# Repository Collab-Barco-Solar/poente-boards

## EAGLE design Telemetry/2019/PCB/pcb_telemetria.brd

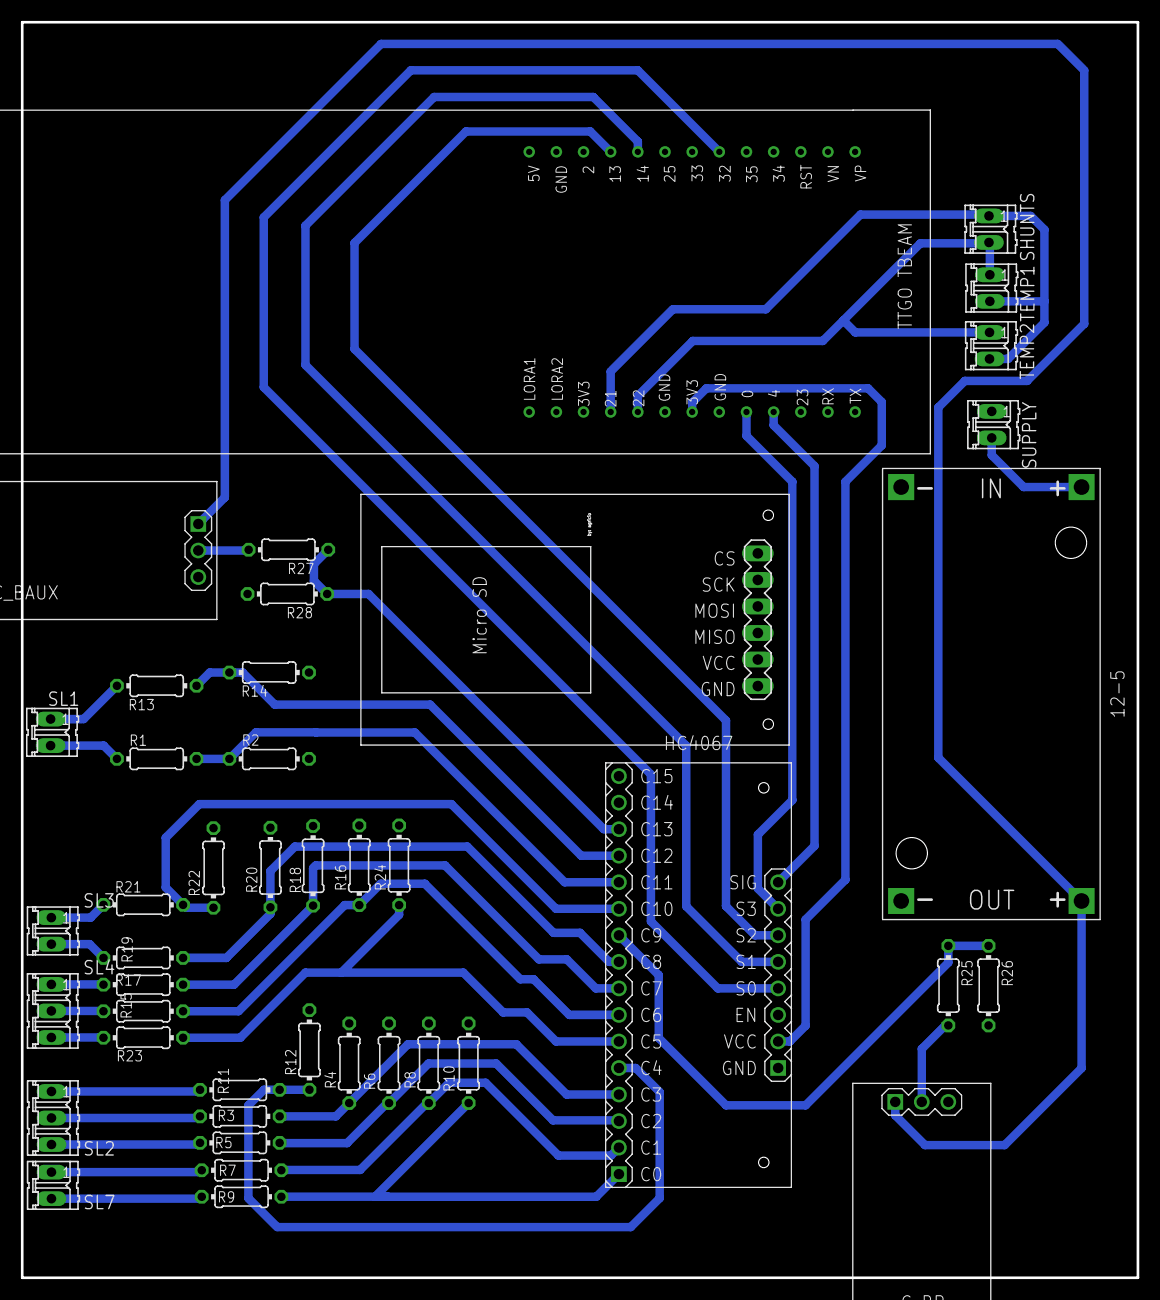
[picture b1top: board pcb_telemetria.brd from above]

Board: 2 copper layers, 106.8 x 120.2 mm, 43 parts (0 on the bottom side), 39 nets.

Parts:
12-5: DC-DC-STEP-DOWN-LM2596
C_BAUX: CURRENT-SENSOR-ACS712
C_BP: CURRENT-SENSOR-ACS712
HC4067: SPARKFUN-AD-MUX-16X1
R1: 330k; 0204/7
R2, R14: 12k; 0204/7
R3, R5, R7, R9, R25, R27: 2.2k; 0204/7
R4, R6, R8, R10, R26, R28: 3.9k; 0204/7
R11, R13: 220k; 0204/7
R12: 390k; 0204/7
R15, R17, R19, R21, R23: 270k; 0204/7
R16, R18, R20, R22, R24: 68k; 0204/7
SHUNTS: 02P
SL1, SL3, SL7: 02P
SL2, SL4: 03P
SUPPLY: 02P
TEMP1, TEMP2: 02P
U$1: TTGOBEAM
U$2: MICRO_SD_MODULE; MICRO_SD

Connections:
0: HC4067.J2.7, U$1.0
3V3: HC4067.J2.2, U$1.3V3
4: HC4067.J2.8, U$1.4
13: HC4067.J2.6, U$1.13
14: HC4067.J2.5, U$1.14
21: SHUNTS.1, TEMP1.2, TEMP2.2, U$1.21
22: SHUNTS.2, TEMP1.1, TEMP2.1, U$1.22
32: HC4067.J2.4, U$1.32
BAT_AUX: R21.2, SL3.1
BAT_BANCO: R13.2, SL1.1
BB_IN: R15.1, SL4.2
BE_IN: R17.2, SL4.1
BTN_CRUZ: R3.1, SL2.2
BTN_M: R5.2, SL2.3
BTN_RE: R7.1, SL7.1
C0: HC4067.J1.1, R9.1, R10.2
C1: HC4067.J1.2, R7.2, R8.1
C2: HC4067.J1.3, R5.1, R6.2
C3: HC4067.J1.4, R3.2, R4.1
C4: HC4067.J1.5, R11.2, R12.1
C5: HC4067.J1.6, R23.2, R24.1
C6: HC4067.J1.7, R15.2, R16.1
C7: HC4067.J1.8, R17.1, R18.2
C8: HC4067.J1.9, R19.2, R20.1
C9: HC4067.J1.10, R25.1, R26.1
C10: HC4067.J1.11, R21.1, R22.2
C11: HC4067.J1.12, R1.1, R2.2
C12: HC4067.J1.13, R13.1, R14.2
C13: HC4067.J1.14, R27.1, R28.1
COOLER_B: R23.1, SL4.3
COOLER_E: R19.1, SL3.2
DMS_IN: R9.2, SL7.2
GND: 12-5.IN-, 12-5.OUT-, C_BAUX.3, C_BP.3, HC4067.J2.1, HC4067.J2.3, R2.1, R4.2, R6.1, R8.2, R10.1, R12.2, R14.1, R16.2, R18.1, R20.2, R22.1, R24.2, R26.2, R28.2, SUPPLY.1, U$1.GND, U$1.GND1
unnamed: C_BP.2, R25.2
unnamed: C_BAUX.2, R27.2
POT_IN: R11.1, SL2.1
PV_IN: R1.2, SL1.2
VCC: 12-5.OUT+, C_BAUX.1, C_BP.1
VI: 12-5.IN+, SUPPLY.2

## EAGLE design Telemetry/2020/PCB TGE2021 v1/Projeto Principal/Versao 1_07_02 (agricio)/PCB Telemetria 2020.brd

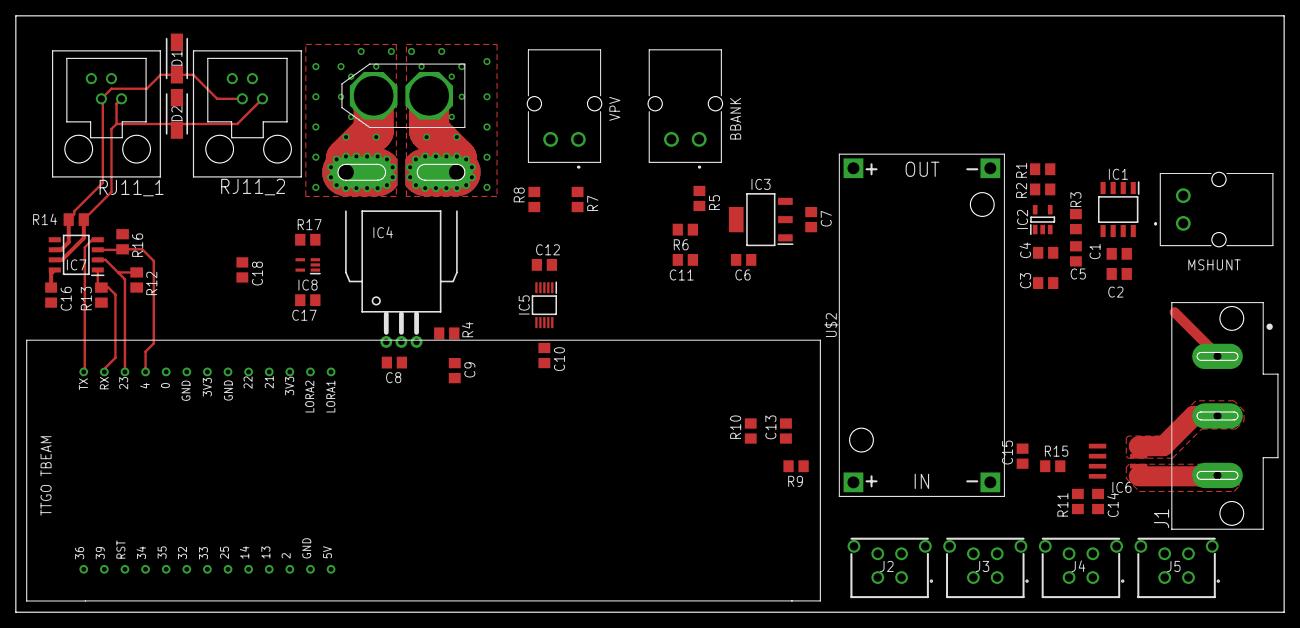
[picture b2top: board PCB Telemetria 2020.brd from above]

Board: 2 copper layers, 160.0 x 75.2 mm, 58 parts (0 on the bottom side), 31 nets.

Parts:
BBANK: 53259-0229; 0532590229
C1, C4, C5, C8, C9, C10, C14, C15, C16, C17: 100nF; C0805
C2: 10nF; C0805
C3: 10uF; C0805
C6, C7: 22uF; C0805
C11, C13: 1nF; C0805
C12: C0805
C18: 680pF; C0805
D1, D2: SMAJ30CA; DIONM5026X229N
IC1: INA240A1DR; SOIC127P600X175-8N
IC2: MCP3221A6T-E_OTVAO; SOT95P280X145-5N
IC3: AZ1117IH-3.3TRG1; SOT230P700X170-4N
IC4: ACS758LCB-050B-PFF-T; CB-PFF
IC5: ADS1115IDGSR; SOP50P490X110-10N
IC6: ACS712-030B3; SOIC8
IC7: THVD2410DR; SOIC127P600X175-8N
IC8: TMP235AEDCKRQ1; SOT65P210X110-5N
J1: 172042-0406; MOLEX_172042-0406
J2, J3, J4, J5: 43045-0412
MSHUNT: 53259-0229; 0532590229
R1, R2, R7, R8: R0805
R3: 680R; R0805
R4, R10, R11, R17: 4.7k; R0805
R5: 220k; R0805
R6: 13.3k; R0805
R9: 16k; R0805
R12, R13, R16: 10k; M0805
R14: 120R; M0805
R15: 1.6k; R0805
RJ11_1, RJ11_2: TFC44
U$1: TTGOBEAM
U$2: DC-DC-STEP-DOWN-LM2596
U$3: XT60
VPV: 53259-0229; 0532590229

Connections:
12V_CM: C15.1, R15.2, U$1.33
12V_CURRENT_M: IC6.1, IC6.2, J1.3
12V_VM: C13.1, R9.2, R10.1, U$1.32
!RXEN: IC7.2, R12.1, U$1.23
BBANK_AIN0: C11.1, IC5.4, R5.2, R6.1
CMPPT_F: C9.1, R4.2
CMPPT_M: IC4.IP-, IC4.IP-@2, IC4.IP-@3, IC4.IP-@4, IC4.IP-@5, IC4.IP-@6, IC4.IP-@7, IC4.IP-@8, IC4.IP-@9, IC4.IP-@10, IC4.IP-@11, IC4.IP-@12, IC4.IP-@13, IC4.IP-@14, IC4.IP-@15, IC4.IP-@16, IC4.IP-@17, U$3.-
CMPPT_OUT: IC4.3, R4.1
CMPPT_P: IC4.IP+, IC4.IP+@2, IC4.IP+@3, IC4.IP+@4, IC4.IP+@5, IC4.IP+@6, IC4.IP+@7, IC4.IP+@8, IC4.IP+@9, IC4.IP+@10, IC4.IP+@11, IC4.IP+@12, IC4.IP+@13, IC4.IP+@14, IC4.IP+@15, IC4.IP+@16, IC4.IP+@17, U$3.+
GND: BBANK.2, C1.2, C2.2, C3.2, C4.2, C5.2, C6.2, C7.2, C8.2, C9.2, C10.2, C11.2, C12.2, C13.2, C14.2, C15.2, C16.2, C17.2, C18.2, D1.2, D2.2, IC1.2, IC1.7, IC2.2, IC3.1, IC4.2, IC5.1, IC5.3, IC6.5, IC7.5, IC8.2, J1.1, R6.2, R8.2, R10.2, R16.1, RJ11_1.P$3, RJ11_2.P$3, U$1.GND, U$1.GND3, U$2.IN-, U$2.OUT-, VPV.2
I2C_SCL: IC2.5, IC5.10, R2.1, U$1.21
I2C_SDA: IC2.4, IC5.9, R1.1, U$1.22
MSHUNT_ADC: C5.1, IC2.3, R3.1
MSHUNT_AMP: IC1.5, R3.2
MSHUNT_B: IC1.8, MSHUNT.1
MSHUNT_M: IC1.1, MSHUNT.2
unnamed: IC6.6, R11.2
unnamed: IC6.7, R15.1
unnamed: IC8.3, R17.1
unnamed: D1.1, IC7.6, R14.1, RJ11_1.P$2, RJ11_2.P$2
unnamed: D2.1, IC7.7, R14.2, RJ11_1.P$4, RJ11_2.P$4
PV_AIN1: C12.1, IC5.5, R7.2, R8.1
TEMP1: C18.1, R17.2, U$1.13
TXEN: IC7.3, R16.2, U$1.4
UART_RX: IC7.1, R13.1, U$1.RX
UART_TX: IC7.4, U$1.TX
VCC_3V3: C1.1, C2.1, C3.1, C4.1, C6.1, C8.1, C10.1, C14.1, C16.1, C17.1, IC1.3, IC1.6, IC2.1, IC3.2, IC3.4, IC4.1, IC5.8, IC6.8, IC7.8, IC8.4, R1.2, R2.2, R11.1, R12.2, R13.2, RJ11_1.P$1, RJ11_2.P$1, U$1.3.3V, U$1.3V3
VCC_5V: C7.1, IC3.3, U$1.5V, U$2.OUT+
VCC_12V: IC6.3, IC6.4, J1.2, R9.1, U$2.IN+
VCC_BBANK: BBANK.1, R5.1
VCC_PV: R7.1, VPV.1

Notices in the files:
parts and their libraries:
diy-modules: Released under the Creative Commons Attribution 4.0 International License: http://creativecommons.org/licenses/by/4.0
